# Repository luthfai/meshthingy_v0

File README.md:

# meshthingy v0

> An off-grid LoRa mesh communicator — a pocket-sized ESP32-S3 node that sends
> text and GPS position over kilometres of open ground, with no cell tower, no
> SIM, no subscription, and no internet.

<sub>KiCad 10 · 2-layer · 71 × 46 mm · ESP32-S3 + SX1262-class LoRa · USB-C · Li-Ion</sub>

---

## What this board is for

Phones stop working the moment you leave coverage. **meshthingy** doesn't need
coverage — it *is* the network.

Each board is one node in a self-healing [Meshtastic](https://meshtastic.org)
mesh. Nodes talk directly to each other over licence-free LoRa radio, and every
node automatically relays traffic for its neighbours. Two units give you a
private long-range walkie-talkie for text; a handful scattered across a valley,
a campsite, a ridgeline, or a city block give everyone in that area a shared
messaging network that keeps working when nothing else does.

Because LoRa trades bandwidth for range and power, a node runs for **days** on a
small Li-Ion cell and reaches **several kilometres** line-of-sight — far past
Wi-Fi or Bluetooth, and without the power budget a cellular radio demands.

Typical uses: hiking and backcountry trips, sailing, off-road convoys, festival
and event crews, neighbourhood emergency preparedness, and as a low-cost
long-range telemetry link for remote sensors.

The onboard GPS, environmental and motion sensors mean a node is useful even
with nobody holding it — drop one on a hilltop as a solar-powered repeater and
it becomes a weather station that also extends everyone's range.

## Features

- **ESP32-S3-WROOM-1** — dual-core MCU with Wi-Fi and Bluetooth LE for phone pairing
- **HT-RA62 LoRa module** — long-range sub-GHz radio, U.FL *and* SMA edge-mount antenna options
- **ATGM336H GNSS** — position reporting, with a rechargeable backup cell for warm starts
- **0.96" OLED** — read messages without a phone
- **BME280** — temperature, humidity, barometric pressure
- **LIS3DSH accelerometer** — wake-on-motion and orientation, with interrupt to the MCU
- **USB-C charging** — BQ24072 Li-Ion charger with power-path, so it runs while charging
- **JST-PH battery connector** — standard single-cell Li-Ion / LiPo
- **Vibration motor driver** — SI2302 low-side switch with flyback diode, for silent alerts in a pocket
- **Buzzer, status LED, and a side lever switch** for headless operation
- **Test points** on every bus for bring-up and debugging

## System architecture

```mermaid
flowchart TB
    subgraph RF["📡 Radio"]
        LORA["<b>U4 · HT-RA62</b><br/>LoRa transceiver"]
        UFL["J3 · U.FL"]
        SMA["J4 · SMA<br/>edge mount"]
        LORA --- UFL
        LORA --- SMA
    end

    subgraph CORE["🧠 Core"]
        MCU["<b>U7 · ESP32-S3-WROOM-1</b><br/>Wi-Fi · BLE · dual core"]
    end

    subgraph NAV["🛰️ Navigation"]
        GPS["<b>U2 · ATGM336H</b><br/>GNSS receiver"]
        EEP["U8 · AT24C32<br/>almanac EEPROM"]
        BAT2["C13 · XH414H<br/>backup cell"]
        GPS -->|"private I²C"| EEP
        BAT2 -.->|"keeps time"| GPS
    end

    subgraph IO["🔌 I²C peripherals"]
        OLED["U1 · 0.96in OLED"]
        BME["U9 · BME280<br/>temp · humidity · pressure"]
        ACC["U10 · LIS3DSH<br/>accelerometer"]
    end

    subgraph UX["🎛️ Interface"]
        BUZ["LS1 · buzzer"]
        LED["D2 · status LED"]
        SW["U5 · lever switch"]
        VIB["Q4 · SI2302<br/>vibration motor"]
    end

    MCU <==>|"<b>SPI</b> + BUSY/RST/DIO1"| LORA
    MCU <-->|"<b>UART</b> + 1PPS"| GPS
    MCU <-->|"<b>I²C</b> · IO13/IO14"| OLED
    MCU <-->|"<b>I²C</b>"| BME
    MCU <-->|"<b>I²C</b> + INT→IO48"| ACC
    MCU --> BUZ
    MCU --> LED
    MCU -->|IO15| VIB
    SW --> MCU

    classDef core fill:#4f46e5,stroke:#3730a3,color:#fff,stroke-width:2px
    classDef radio fill:#0891b2,stroke:#0e7490,color:#fff
    classDef nav fill:#059669,stroke:#047857,color:#fff
    classDef periph fill:#d97706,stroke:#b45309,color:#fff
    classDef ux fill:#7c3aed,stroke:#6d28d9,color:#fff
    class MCU core
    class LORA,UFL,SMA radio
    class GPS,EEP,BAT2 nav
    class OLED,BME,ACC periph
    class BUZ,LED,SW,VIB ux
```

## Power path

USB-C and the battery both feed a power-path charger, so the node keeps running
while it charges and switches over seamlessly when USB is unplugged.

```mermaid
flowchart LR
    USB["<b>J1</b><br/>USB-C<br/>5 V in"] -->|VBUS| CHG
    BATT["<b>J2</b><br/>Li-Ion cell<br/>JST-PH"] <-->|charge / discharge| CHG
    CHG["<b>U6 · BQ24072</b><br/>Li-Ion charger<br/>+ power path"] -->|VSYS| BUCK
    BUCK["<b>U3 · TPS62046</b><br/>step-down<br/>via L2"] -->|"+3V3"| RAIL

    RAIL["<b>+3V3 rail</b>"] --> M1["ESP32-S3"]
    RAIL --> M2["LoRa"]
    RAIL --> M3["GNSS"]
    RAIL --> M4["Sensors + OLED"]
    RAIL --> M5["Buzzer + vib motor"]

    classDef src fill:#dc2626,stroke:#991b1b,color:#fff,stroke-width:2px
    classDef conv fill:#ea580c,stroke:#c2410c,color:#fff,stroke-width:2px
    classDef rail fill:#16a34a,stroke:#15803d,color:#fff,stroke-width:2px
    classDef load fill:#475569,stroke:#334155,color:#fff
    class USB,BATT src
    class CHG,BUCK conv
    class RAIL rail
    class M1,M2,M3,M4,M5 load
```

## Board

| | |
| --- | --- |
| **Dimensions** | 71.00 × 46.00 mm, 1.0 mm corner radius |
| **Stackup** | 2 layers (F.Cu / B.Cu), 1.6 mm |
| **Components** | 91 footprints, 350 pads (326 SMD, 22 through-hole, 2 NPTH), 373 vias |
| **Density** | 66% front, 9% back — almost everything lives on the front |
| **Copper** | GND pour on both layers, with keepout zones under the antennas |
| **Routing** | Rounded track corners throughout (see `meshtastic-v0.round-tracks-config`) |
| **Design rules** | 0.175 mm clearance, 0.2 mm minimum track, 0.6 / 0.3 mm vias |
| **Assembly** | All SMD, 0805 passives — hand-solderable |

Everything routes on two layers, which keeps this a cheap board to order from any
prototype fab at standard tolerances.

### Assembled views

<table>
  <tr>
    <td width="50%" align="center">
      <br>
      <sub><b>Front</b> — LoRa and GNSS modules, ESP32-S3, USB-C, buzzer, GPS backup cell, motor driver</sub>
    </td>
    <td width="50%" align="center">
      <br>
      <sub><b>Back</b> — labelled test points for every bus, vibration motor pads (<code>JP1</code>), SMA edge launch</sub>
    </td>
  </tr>
</table>

### PCB layer views

Copper, silkscreen and board outline, plotted straight from the layout. The back
view is mirrored so its silkscreen reads the right way round.

<table>
  <tr>
    <td width="50%" align="center">
      <br>
      <sub><b>F.Cu + F.SilkS</b> — signal routing over the front ground pour; <code>B</code>/<code>R</code> are the boot and reset pads</sub>
    </td>
    <td width="50%" align="center">
      <br>
      <sub><b>B.Cu + B.SilkS</b> — mirrored; back pour with the test-point field and motor pads</sub>
    </td>
  </tr>
</table>

The RF section is deliberately sparse: the pours are cut back under both antenna
launches, and the GPS patch keepout is marked on the silkscreen so nothing gets
placed under it during assembly.

Regenerate these plots after any layout change:

```bash
kicad-cli pcb export svg --output docs/layers-front.svg \
  --layers "F.Cu,F.SilkS,Edge.Cuts" \
  --page-size-mode 2 --exclude-drawing-sheet --check-zones --mode-single \
  meshtastic-v0.kicad_pcb

kicad-cli pcb export svg --output docs/layers-back.svg \
  --layers "B.Cu,B.SilkS,Edge.Cuts" --mirror \
  --page-size-mode 2 --exclude-drawing-sheet --check-zones --mode-single \
  meshtastic-v0.kicad_pcb
```

## Pin map

| Function | ESP32-S3 pin | Goes to |
| --- | --- | --- |
| LoRa SCK | TXD0 / GPIO43 | `U4` pin 12 |
| LoRa data | IO1, IO2 | `U4` pins 13, 14 |
| LoRa CS | IO6 | `U4` NSS |
| LoRa DIO1 | IO4 | `U4` interrupt |
| LoRa RESET | IO5 | `U4` reset |
| LoRa BUSY | RXD0 / GPIO44 | `U4` pin 10 |
| GPS TX → MCU | IO42 | `U2` TXD |
| GPS RX ← MCU | IO41 | `U2` RXD |
| GPS 1PPS | IO40 | `U2` timing pulse |
| GPS RESET / enable | IO38, IO39 | `U2` |
| I²C SDA / SCL | IO13 / IO14 | OLED, BME280, LIS3DSH |
| Accelerometer INT | IO48 | `U10` INT1 |
| Vibration motor | IO15 | `Q4` gate (10k pull-down `R23`) |
| Buzzer | IO16 | `Q1` gate (10k pull-down `R11`) |
| Status LED | IO21 | `D2` via `R22` |
| Spare / test | IO7, IO47 | back-side test points `IO7`, `IO47` |

## Schematic layout

The design is hierarchical — root sheet [meshtastic-v0.kicad_sch](meshtastic-v0.kicad_sch):

| Sheet | Contents |
| --- | --- |
| [Power Management](Power%20Management.kicad_sch) | BQ24072 charger, TPS62046 buck, load switching |
| [Microcontroller](Microcontroller.kicad_sch) | ESP32-S3-WROOM-1, boot and reset pads |
| [LORA](LORA.kicad_sch) | HT-RA62 module, U.FL and SMA antenna paths |
| [GPS](GPS.kicad_sch) | ATGM336H, AT24C32 EEPROM, backup cell |
| [Display](Display.kicad_sch) | 0.96" OLED and its pinout-select jumpers |
| [Air Sensors](Air%20Sensors.kicad_sch) | BME280 |
| [Accelerometer](Accelerometer.kicad_sch) | LIS3DSH |
| [Peripherals](Peripherals.kicad_sch) | Buzzer and vibration motor drivers, status LED, test points |
| [Connectors](Connectors.kicad_sch) | USB-C receptacle, JST-PH battery |

## Building it

Open [meshtastic-v0.kicad_pro](meshtastic-v0.kicad_pro) in **KiCad 10** or newer.
All custom symbols and footprints live in [libs/](libs/) and are referenced through
`${KIPRJMOD}`, so the project is self-contained — clone and open, nothing else to install.

Generate fabrication files from the command line:

```bash
# Gerbers + drill, ready to zip and upload to a fab
kicad-cli pcb export gerbers --output fab/ meshtastic-v0.kicad_pcb
kicad-cli pcb export drill   --output fab/ meshtastic-v0.kicad_pcb

# Bill of materials and pick-and-place
kicad-cli sch export bom       --output bom.csv meshtastic-v0.kicad_sch
kicad-cli pcb export pos       --output pos.csv meshtastic-v0.kicad_pcb

# 3D render
kicad-cli pcb render --output board.png meshtastic-v0.kicad_pcb
```

Generated outputs are gitignored — regenerate them, or attach them to a release tag.

### Assembly note

`JP3` and `JP4` are three-way solder jumpers that select which OLED pin gets
`+3V3` and which gets `GND`, so the footprint accepts display modules with either
pinout. They ship **unbridged** — bridge them to match the module you source
before expecting the display to light up.

`JP1` on the back is not a jumper. It's the pair of solder pads for the vibration
motor. Solder a coin or pager-style motor's leads across it: the pad on the
`+3V3` side takes the red lead and the pad on the `Q4` drain side takes the black
lead. `D9` clamps the motor's flyback, so the motor runs straight off the
`+3V3` rail.

`B` and `R` on the front are the **BOOT** and **RESET** pads. To put the ESP32-S3
into the ROM bootloader, short `B` while you tap `R`.

## Firmware

The board targets [Meshtastic](https://meshtastic.org) firmware on the ESP32-S3.
Peripheral pin assignments follow the map above; the ESP32-S3 GPIO matrix means
bus pins are remappable in firmware if a variant config needs to differ.

## Repository notes

`.history/` is KiCad 10's Local History — a separate nested git repository of
autosaves. It is gitignored and should stay that way. Delete it freely if you
don't need the local undo history.

---

<sub>Meshtastic® is a registered trademark of Meshtastic LLC. This is an
independent hardware design and is not affiliated with or endorsed by Meshtastic LLC.</sub>

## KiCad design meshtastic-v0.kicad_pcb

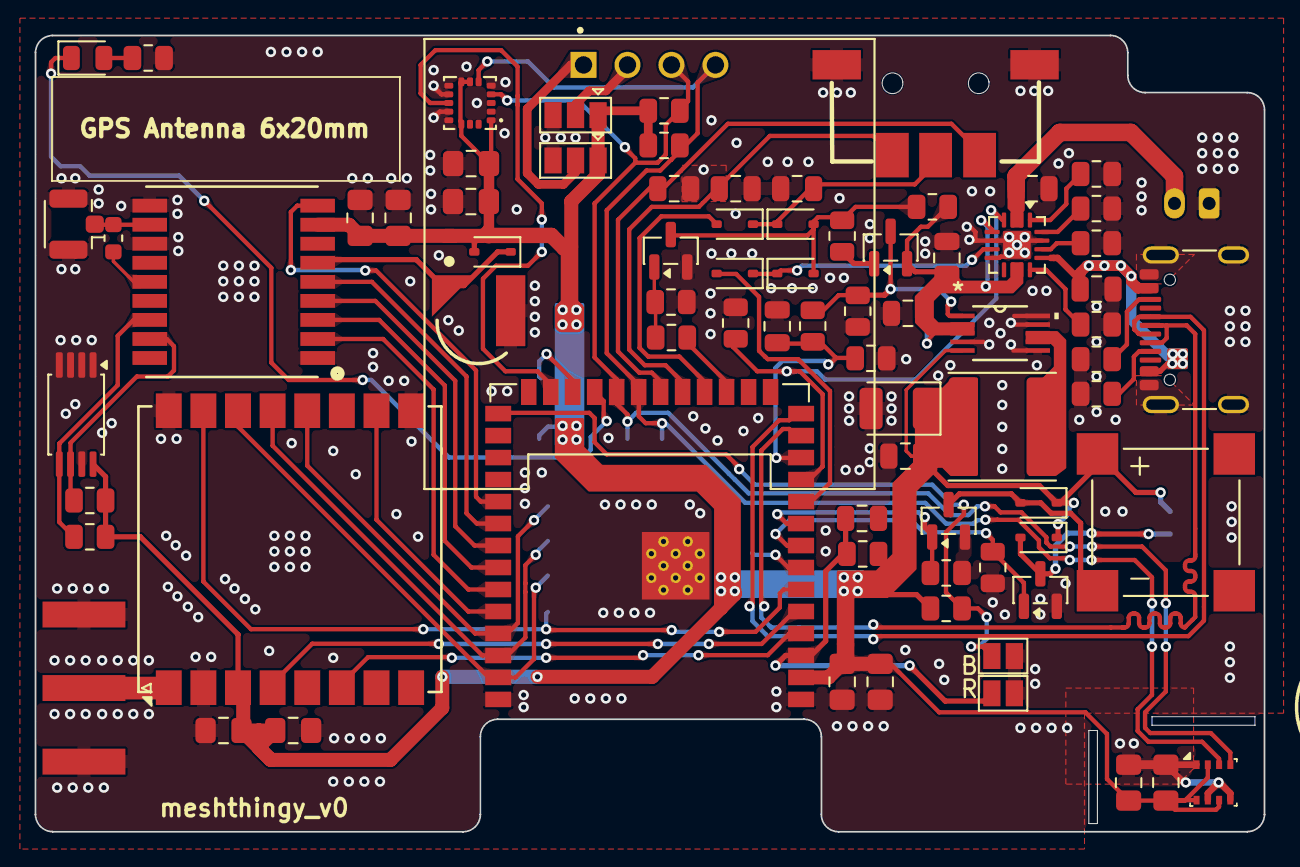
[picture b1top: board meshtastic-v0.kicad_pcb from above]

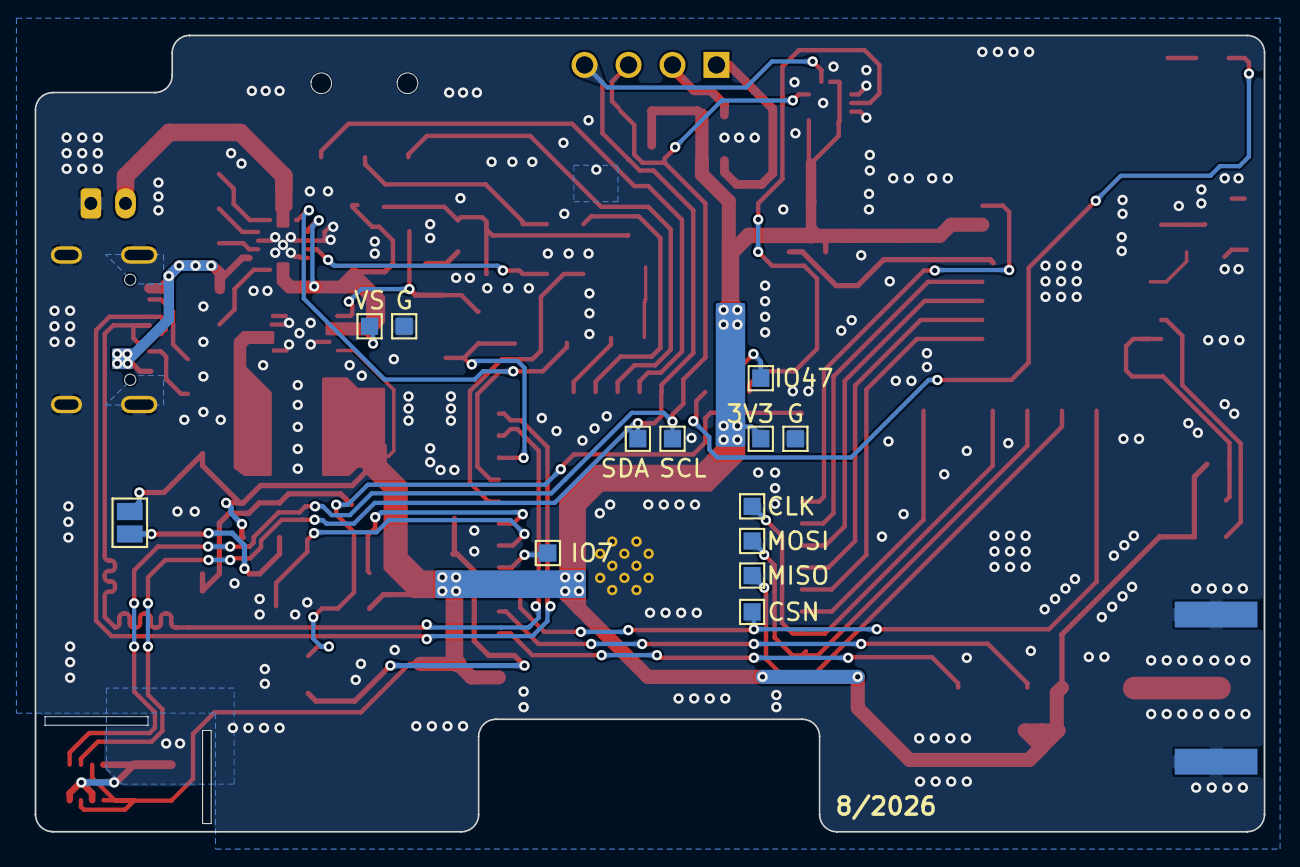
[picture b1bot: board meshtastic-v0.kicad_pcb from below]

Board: 2 copper layers, 71.0 x 46.0 mm, 91 parts (13 on the bottom side), 60 nets.

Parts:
3V3: 3V3; TestPoint_Pad_1.0x1.0mm
B: Boot; SolderJumper-2_P1.3mm_Open_Pad1.0x1.5mm
C1, C10, C19, C21, C23, C24: 100nF; C_0805_2012Metric_Pad1.18x1.45mm_HandSolder
C2, C9, C18, C20: 10uF; C_0805_2012Metric_Pad1.18x1.45mm_HandSolder
C3, C5: 4u7; C_0805_2012Metric
C4, C6, C17: 1u; C_0805_2012Metric
C7, C8, C11: 100n; C_0805_2012Metric
C12: 22u; C_0805_2012Metric
C13: XH414H-IV01E; CAP_XH414H-IV01E
C14: 10u; C_0805_2012Metric
C16: 22u; CP_EIA-3528-15_AVX-H
CLK: CLK; TestPoint_Pad_1.0x1.0mm
CSN: CSN; TestPoint_Pad_1.0x1.0mm
D1: 1N4148WS; D_SOD-323
D2: LED; LED_0805_2012Metric
D4, D5, D6, D7, D8, D9: 1N5819WS; D_SOD-323
G: GND; TestPoint_Pad_1.0x1.0mm
G#2: GND; TestPoint_Pad_1.0x1.0mm
IO7: IO15; TestPoint_Pad_1.0x1.0mm
IO47: IO47; TestPoint_Pad_1.0x1.0mm
J1: USB_C_Receptacle_USB2.0_16P; USB_C_Receptacle_G-Switch_GT-USB-7010ASV
J2: Conn_01x02_Pin; JST_PH_S2B-PH-K_1x02_P2.00mm_Horizontal
J3: Conn_Coaxial; U.FL_Hirose_U.FL-R-SMT-1_Vertical
J4: Conn_Coaxial; SMA_Amphenol_132289_EdgeMount
JP1: SolderJumper_2_Open; SolderJumper-2_P1.3mm_Open_Pad1.0x1.5mm
JP3, JP4: EN1; SolderJumper-3_P1.3mm_Open_Pad1.0x1.5mm
L1: 47nH; L_0603_1608Metric
L2: 6.8u; L_Changjiang_FNR6045S
LS1: SMT-0927-S-14-R; XDCR_SMT-0927-S-14-R
MISO: MISO; TestPoint_Pad_1.0x1.0mm
MOSI: MOSI; TestPoint_Pad_1.0x1.0mm
Q1, Q4: SI2302; SOT-23
Q2: Q_PNP_BEC; SOT-23
Q3: Q_NPN_BEC; SOT-23
R: Reset; SolderJumper-2_P1.3mm_Open_Pad1.0x1.5mm
R1, R2: 5k1; R_0805_2012Metric
R3, R6, R7, R8, R9, R11, R19, R20, R23: 10k; R_0805_2012Metric
R4, R22: 1k; R_0805_2012Metric
R5: 1k2; R_0805_2012Metric
R10, R12, R13, R21: 4k7; R_0805_2012Metric
R14, R15, R16, R17, R18: 100k; R_0805_2012Metric
SCL: SCL; TestPoint_Pad_1.0x1.0mm
SDA: SDA; TestPoint_Pad_1.0x1.0mm
U1: DM-OLED096-636; MODULE_DM-OLED096-636
U2: ATGM336H; ATGM336H-5N
U3: TPS62046DGQR; DGQ10_1P88X1P57
U4: HT-RA62; Ai-Thinker-Ra-01-LoRa
U5: Lever Switch TMHU26; tmhu26
U6: BQ24072RGT; VQFN-16-1EP_3x3mm_P0.5mm_EP1.6x1.6mm
U7: ESP32-S3-WROOM-1
U8: AT24C32A; TSSOP-8_4.4x3mm_P0.65mm
U9: BME280; Bosch_LGA-8_2.5x2.5mm_P0.65mm_ClockwisePinNumbering
U10: LIS3DSHTR; LGA16R50P5X3_300X300X100N
VS: VS; TestPoint_Pad_1.0x1.0mm

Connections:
+3V3: 3V3.1 (1_1), C1.1, C2.1, C9.1, C10.1, C14.2, C16.1, C18.1, C19.1, C20.1, C21.1, C23.1, C24.1, D1.2 (A), D5.1 (K), D9.1 (K), JP1.2 (B), JP3.1 (A), JP4.1 (A), L2.2, LS1.P, R10.2, R12.1, R13.1, R19.1, R20.1, R21.2, U2.8 (VCC), U3.5 (FB), U4.3 (3V3), U7.2 (3V3), U8.8 (VCC), U9.2 (CSB), U9.6 (VDDIO), U9.8 (VDD), U10.1 (VDD_IO), U10.7 (SDO/SA0), U10.8 (CS), U10.14 (VDD)
/Accelerometer/INT: U7.25 (IO48), U10.11 (INT1)
/Accelerometer/SCL: R10.1, SCL.1 (1_1), U1.3 (SCL), U7.22 (IO14), U9.4 (SCK), U10.4 (SCL/SPC)
/Accelerometer/SDA: R12.2, SDA.1 (1_1), U1.4 (SDA), U7.21 (IO13), U9.3 (SDI), U10.6 (SDA/SDI/SDO)
/Connectors/D+: J1.A6 (D+), J1.B6 (D+), U7.14 (USB_D+)
/Connectors/D-: J1.A7 (D-), J1.B7 (D-), U7.13 (USB_D-)
/Connectors/VBATT: C5.1, J2.2, U6.2 (BAT), U6.3 (BAT)
/Connectors/VBUS: C4.2, J1.A4 (VBUS), J1.A9 (VBUS), J1.B4 (VBUS), J1.B9 (VBUS), U6.13 (IN)
/GPS/GPS_EN: U2.5 (ON/OFF), U7.32 (IO39)
/GPS/GPS_PPS: U2.4 (1PPS), U7.33 (IO40)
/GPS/GPS_RST: U2.9 (nRESET), U7.31 (IO38)
/GPS/GPS_RX: U2.3 (RXD), U7.34 (IO41)
/GPS/GPS_SCL: R21.1, U2.17 (SCL), U8.6 (SCL)
/GPS/GPS_SDA: R13.2, U2.16 (SDA), U8.5 (SDA)
/GPS/GPS_TX: U2.2 (TXD), U7.35 (IO42)
/GPS/GPS_VBATT: C13.1, D1.1 (K), U2.6 (VBAT)
/LORA/LORA_BUSY: U4.10 (BUSY), U7.36 (RXD0)
/LORA/LORA_INT: U4.6 (DIO1), U7.4 (IO4)
/LORA/LORA_RST: U4.4 (~RESET), U7.5 (IO5)
/LORA/SPI2_CLK: CLK.1 (1_1), U4.12 (SCK), U7.37 (TXD0)
/LORA/SPI2_CS_N: CSN.1 (1_1), U4.15 (~NSS), U7.6 (IO6)
/LORA/SPI2_MISO: MISO.1 (1_1), U4.14 (MOSI), U7.39 (IO1)
/LORA/SPI2_MOSI: MOSI.1 (1_1), U4.13 (MISO), U7.38 (IO2)
/Microcontroller/BAT_ADC: C6.1, R16.1, R17.2, U7.12 (IO8)
/Microcontroller/BOOT: B.2 (B), R20.2, U7.27 (IO0)
/Microcontroller/BUZZER: Q1.1 (G), R11.2, U7.9 (IO16)
/Microcontroller/CHG_EN: R7.1, U6.4 (~CE), U7.11 (IO18)
/Microcontroller/IO07: IO7.1 (1_1), U7.7 (IO7)
/Microcontroller/IO47: IO47.1 (1_1), U7.24 (IO47)
/Microcontroller/PUSH_CCW: C7.1, U5.2, U7.19 (IO11)
/Microcontroller/PUSH_CW: C11.1, U5.1, U7.20 (IO12)
/Microcontroller/PUSH_DWN_MCU: D7.2 (A), U7.18 (IO10)
/Microcontroller/P_GOOD: D4.2 (A), U7.10 (IO17)
/Microcontroller/RESET: C17.2, R.2 (B), R19.2, U7.3 (EN)
/Microcontroller/STATUS_LED: D2.1 (K), U7.23 (IO21)
/Microcontroller/SYS_EN: R9.1, U7.17 (IO9)
/Microcontroller/VIB_MTR: Q4.1 (G), R23.2, U7.8 (IO15)
/Power Management/BUCK_EN: Q2.3 (C), R15.2, R16.2, U3.1 (EN)
/Power Management/PGOOD: D4.1 (K), D6.1 (K), U6.7 (~PGOOD)
/Power Management/PUSH_DWN: C8.1, D7.1 (K), D8.1 (K), U5.4
GND: B.1 (A), C1.2, C2.2, C3.2, C4.1, C5.2, C6.2, C7.2, C8.2, C9.2, C10.2, C11.2, C12.2, C13.2, C14.1, C16.2, C17.1, C18.2, C19.2, C20.2, C21.2, C23.2, C24.2, G.1 (1_1), G#2.1 (1_1), J1.A1 (GND), J1.A12 (GND), J1.B1 (GND), J1.B12 (GND), J1.SH (SHIELD), J2.1, J3.2 (Ext), J4.2 (Ext), JP3.3 (B), JP4.3 (B), Q1.2 (S), Q3.2 (E), Q4.2 (S), R.1 (A), R1.2, R2.2, R3.2, R4.2, R5.2, R6.2, R7.2, R11.1, R15.1, R17.1, R18.1, R22.1, R23.1, U2.1 (GND), U2.10 (GND), U2.12 (GND), U3.4 (GND), U3.6 (MODE), U3.9 (PGND), U3.10 (PGND), U4.2 (GND), U4.9 (GND), U4.16 (GND), U5.3, U5.5, U6.6 (EN1), U6.8 (VSS), U6.15 (TD), U6.17 (VSS), U7.1 (GND), U7.40 (GND), U7.41 (GND), U8.1 (A0), U8.2 (A1), U8.3 (A2), U8.4 (GND), U8.7 (WP), U9.1 (GND), U9.5 (SDO), U9.7 (GND), U10.5 (GND), U10.10 (RES), U10.12 (GND)
unnamed: D2.2 (A), R22.2
unnamed: D5.2 (A), LS1.N, Q1.3 (D)
unnamed: D6.2 (A), D8.2 (A), Q3.3 (C), R8.1, R14.1
unnamed: D9.2 (A), JP1.1 (A), Q4.3 (D)
unnamed: J1.A5 (CC1), R2.1
unnamed: J1.B5 (CC2), R1.1
unnamed: J3.1 (In), L1.1, U2.11 (RF_IN)
unnamed: J4.1 (In), U4.1 (ANT)
unnamed: JP3.2 (C), U1.2 (VCC_IN)
unnamed: JP4.2 (C), U1.1 (GND)
unnamed: L2.1, U3.7 (SW), U3.8 (SW)
unnamed: Q2.1 (B), R8.2
unnamed: Q3.1 (B), R9.2, R18.2
unnamed: L1.2, U2.14 (VCC_RF)
unnamed: R5.1, U6.12 (ILIM)
unnamed: R4.1, U6.16 (ISET)
unnamed: R6.1, U6.14 (TMR)
unnamed: R3.1, U6.1 (TS)
VSYS: C3.1, C12.1, Q2.2 (E), R14.2, U3.2 (VIN), U3.3 (VIN), U6.5 (EN2), U6.10 (OUT), U6.11 (OUT), VS.1 (1_1)
